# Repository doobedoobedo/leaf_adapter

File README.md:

# leaf_adapter

Adapter PCB for the https://www.openinverter.org Brain Board Rev 3 avialable https://openinverter.org/shop/
to fit in a Gen 2 Nissan Leaf inverter.

There are two PCBs one through hole, the other SMD. SMD components are 0603 size

https://www.openinverter.org
Original design © 2018 Johannes Huebner https://github.com/jsphuebner/inverter-hardware/blob/master/leaf_adapter.fpc

# License
Attribution-ShareAlike 4.0 International
https://creativecommons.org/licenses/by-sa/4.0/legalcode

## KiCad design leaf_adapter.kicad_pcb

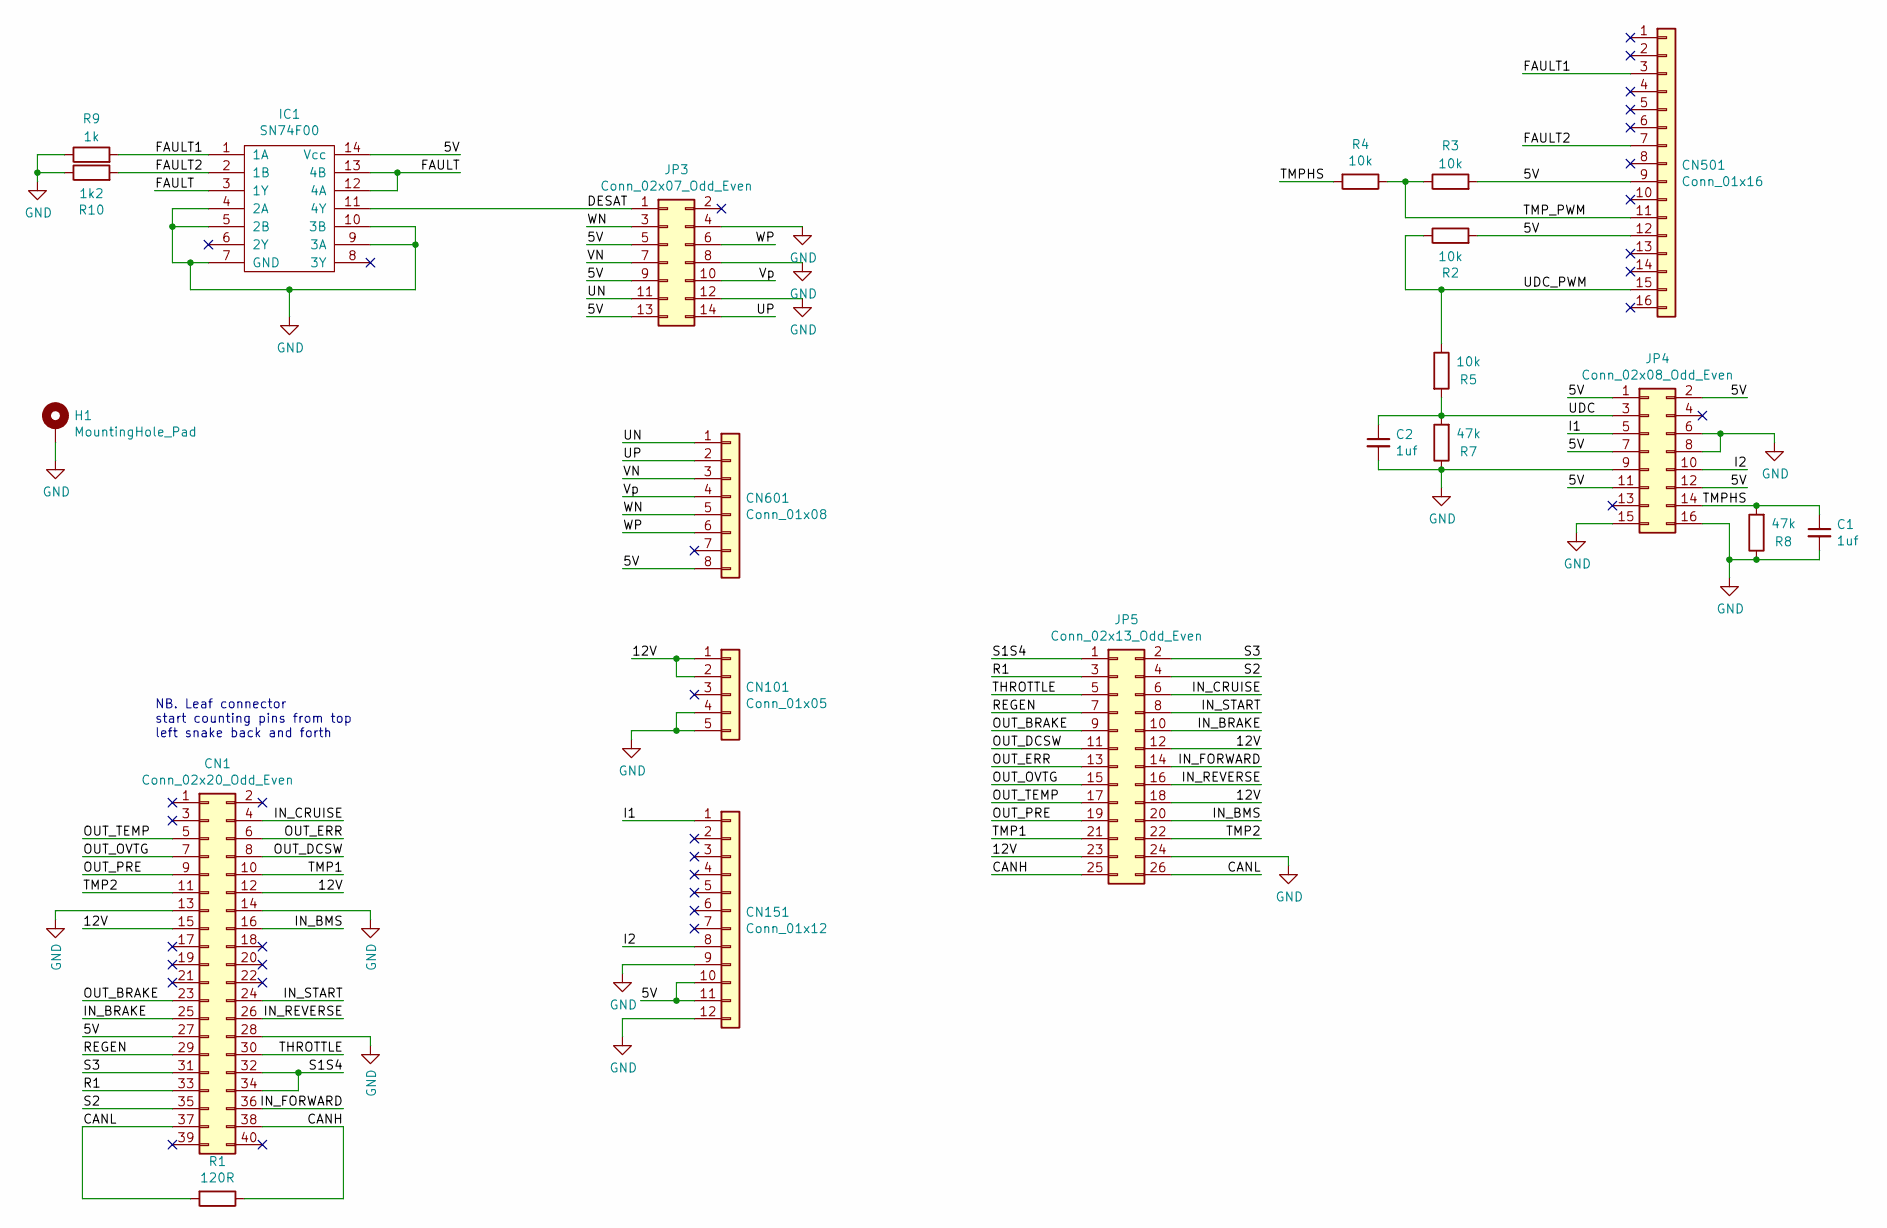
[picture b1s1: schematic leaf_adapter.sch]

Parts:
C1, C2: 1uf; C_0603_HandSoldering
CN1: Conn_02x20_Odd_Even; 1939561-3
CN101: Conn_01x05; GT8E-5P-DS
CN151: Conn_01x12; GT8E-12DP-DS
CN501: Conn_01x16; GT8E-16DP-DS
CN601: Conn_01x08; GT8E-8P-DS
H1: MountingHole_Pad; MountingHole_5.3mm_M5_Pad_Via
IC1: SN74F00; SOIC-14_3.9x8.7mm_Pitch1.27mm
JP3: Conn_02x07_Odd_Even; Socket_Strip_Straight_2x07_Pitch2.54mm
JP4: Conn_02x08_Odd_Even; Socket_Strip_Straight_2x08_Pitch2.54mm
JP5: Conn_02x13_Odd_Even; Socket_Strip_Straight_2x13_Pitch2.54mm
R1: 120R; R_0603_HandSoldering
R2, R3, R4, R5: 10k; R_0603_HandSoldering
R7, R8: 47k; R_0603_HandSoldering
R9: 1k; R_0603_HandSoldering
R10: 1k2; R_0603_HandSoldering

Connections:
/5V: CN1.27, CN151.10, CN151.11, CN501.9, CN501.12, CN601.8, IC1.14 (Vcc), JP3.5, JP3.9, JP3.13, JP4.1, JP4.2, JP4.7, JP4.11, JP4.12, R2.2, R3.2; also elsewhere on the board
/12V: CN1.12, CN1.15, CN101.1, CN101.2, JP5.12, JP5.18, JP5.23; also elsewhere on the board
/CANH: CN1.38, JP5.25, R1.1; also elsewhere on the board
/CANL: CN1.37, JP5.26, R1.2; also elsewhere on the board
/DESAT: IC1.11 (4Y), JP3.1
/FAULT: IC1.3 (1Y), IC1.12 (4A), IC1.13 (4B)
/FAULT1: CN501.3, IC1.1 (1A), R9.2
/FAULT2: CN501.7, IC1.2 (1B), R10.2
/I1: CN151.1, JP4.5
/I2: CN151.8, JP4.10
/IN_BMS: CN1.16, JP5.20; also elsewhere on the board
/IN_BRAKE: CN1.25, JP5.10; also elsewhere on the board
/IN_CRUISE: CN1.4, JP5.6; also elsewhere on the board
/IN_FORWARD: CN1.36, JP5.14; also elsewhere on the board
/IN_REVERSE: CN1.26, JP5.16; also elsewhere on the board
/IN_START: CN1.24, JP5.8; also elsewhere on the board
/OUT_BRAKE: CN1.23, JP5.9; also elsewhere on the board
/OUT_DCSW: CN1.8, JP5.11; also elsewhere on the board
/OUT_ERR: CN1.6, JP5.13; also elsewhere on the board
/OUT_OVTG: CN1.7, JP5.15; also elsewhere on the board
/OUT_PRE: CN1.9, JP5.19; also elsewhere on the board
/OUT_TEMP: CN1.5, JP5.17; also elsewhere on the board
/R1: CN1.33, JP5.3; also elsewhere on the board
/REGEN: CN1.29, JP5.7; also elsewhere on the board
/S1S4: CN1.32, CN1.34, JP5.1; also elsewhere on the board
/S2: CN1.35, JP5.4; also elsewhere on the board
/S3: CN1.31, JP5.2; also elsewhere on the board
/THROTTLE: CN1.30, JP5.5; also elsewhere on the board
/TMP1: CN1.10, JP5.21; also elsewhere on the board
/TMP2: CN1.11, JP5.22; also elsewhere on the board
/TMPHS: C1.1, JP4.14, R4.2, R8.2
/TMP_PWM: CN501.11, R3.1, R4.1
/UDC: C2.1, JP4.3, R5.2, R7.2
/UDC_PWM: CN501.15, R2.1, R5.1
/UN: CN601.1, JP3.11
/UP: CN601.2, JP3.14
/VN: CN601.3, JP3.7
/Vp: CN601.4, JP3.10
/WN: CN601.5, JP3.3
/WP: CN601.6, JP3.6
GND: C1.2, C2.2, CN1.13, CN1.14, CN1.28, CN101.4, CN101.5, CN151.9, CN151.12, H1.1, IC1.4 (2A), IC1.5 (2B), IC1.7 (GND), IC1.9 (3A), IC1.10 (3B), JP3.4, JP3.8, JP3.12, JP4.6, JP4.8, JP4.9, JP4.15, JP4.16, JP5.24, R7.1, R8.1, R9.1, R10.1; also elsewhere on the board

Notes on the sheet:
NB. Leaf connector start counting pins from top left snake back and forth

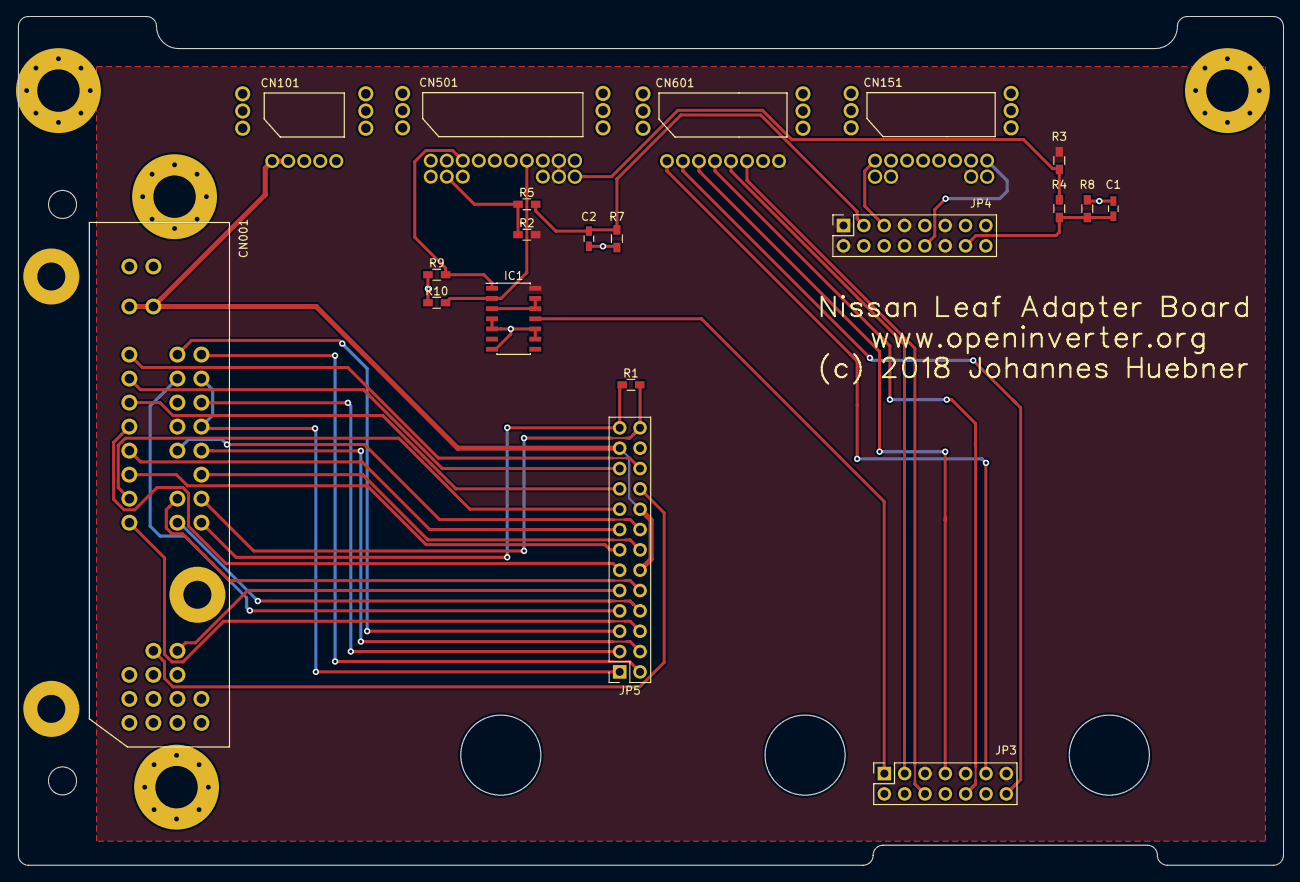
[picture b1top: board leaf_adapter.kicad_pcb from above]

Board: 2 copper layers, 158.0 x 106.0 mm, 21 parts (0 on the bottom side), 41 nets.

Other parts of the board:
CN001: Conn_02x20_Odd_Even; 1939561-3

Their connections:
/5V: CN001.27; also elsewhere on the board
/12V: CN001.12, CN001.15; also elsewhere on the board
/CANH: CN001.38; also elsewhere on the board
/CANL: CN001.37; also elsewhere on the board
/IN_BMS: CN001.16; also elsewhere on the board
/IN_BRAKE: CN001.25; also elsewhere on the board
/IN_CRUISE: CN001.4; also elsewhere on the board
/IN_FORWARD: CN001.36; also elsewhere on the board
/IN_REVERSE: CN001.26; also elsewhere on the board
/IN_START: CN001.24; also elsewhere on the board
/OUT_BRAKE: CN001.23; also elsewhere on the board
/OUT_DCSW: CN001.8; also elsewhere on the board
/OUT_ERR: CN001.6; also elsewhere on the board
/OUT_OVTG: CN001.7; also elsewhere on the board
/OUT_PRE: CN001.9; also elsewhere on the board
/OUT_TEMP: CN001.5; also elsewhere on the board
/R1: CN001.33; also elsewhere on the board
/REGEN: CN001.29; also elsewhere on the board
/S1S4: CN001.32, CN001.34; also elsewhere on the board
/S2: CN001.35; also elsewhere on the board
/S3: CN001.31; also elsewhere on the board
/THROTTLE: CN001.30; also elsewhere on the board
/TMP1: CN001.10; also elsewhere on the board
/TMP2: CN001.11; also elsewhere on the board
GND: CN001.13, CN001.14, CN001.28; also elsewhere on the board

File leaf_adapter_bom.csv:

Reference, Value, Footprint, Datasheet
"C1","1uf","Capacitors_SMD:C_0603_HandSoldering","~"
"C2","1uf","Capacitors_SMD:C_0603_HandSoldering","~"
"R1","120R","Resistors_SMD:R_0603_HandSoldering","~"
"R2","10k","Resistors_SMD:R_0603_HandSoldering","~"
"R3","10k","Resistors_SMD:R_0603_HandSoldering","~"
"R4","10k","Resistors_SMD:R_0603_HandSoldering","~"
"R5","10k","Resistors_SMD:R_0603_HandSoldering","~"
"R7","47k","Resistors_SMD:R_0603_HandSoldering","~"
"R8","47k","Resistors_SMD:R_0603_HandSoldering","~"
"R9","1k","Resistors_SMD:R_0603_HandSoldering","~"
"R10","1k2","Resistors_SMD:R_0603_HandSoldering","~"
"IC1","SN74F00","Housings_SOIC:SOIC-14_3.9x8.7mm_Pitch1.27mm",""
"JP3","Conn_02x07_Odd_Even","Socket_Strips:Socket_Strip_Straight_2x07_Pitch2.54mm","~"
"JP5","Conn_02x13_Odd_Even","Socket_Strips:Socket_Strip_Straight_2x13_Pitch2.54mm","~"
"CN1","Conn_02x20_Odd_Even","Leaf:1939561-3","~"
"CN101","Conn_01x05","GT8E:GT8E-5P-DS","~"
"CN501","Conn_01x16","GT8E:GT8E-16DP-DS","~"
"CN601","Conn_01x08","GT8E:GT8E-8P-DS","~"
"CN151","Conn_01x12","GT8E:GT8E-12DP-DS","~"
"JP4","Conn_02x08_Odd_Even","Socket_Strips:Socket_Strip_Straight_2x08_Pitch2.54mm","~"
"H1","MountingHole_Pad","Mounting_Holes:MountingHole_5.3mm_M5_Pad_Via","~"

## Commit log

2019-07-27 Connector pin mapping
2019-07-29 README updated to include licence
2019-07-29 README updated to include link to original source
